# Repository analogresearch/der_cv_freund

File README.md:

# LITTLE████ CV Modul

Am CV Output liegt immer der Wert vom LB Input.
Am LB Output liegt wenn CV Input nicht eingesteckt ist der Wert vom LB Input.
         "     ... wenn CV Input eingesteckt ist der Wert vom CV Input.

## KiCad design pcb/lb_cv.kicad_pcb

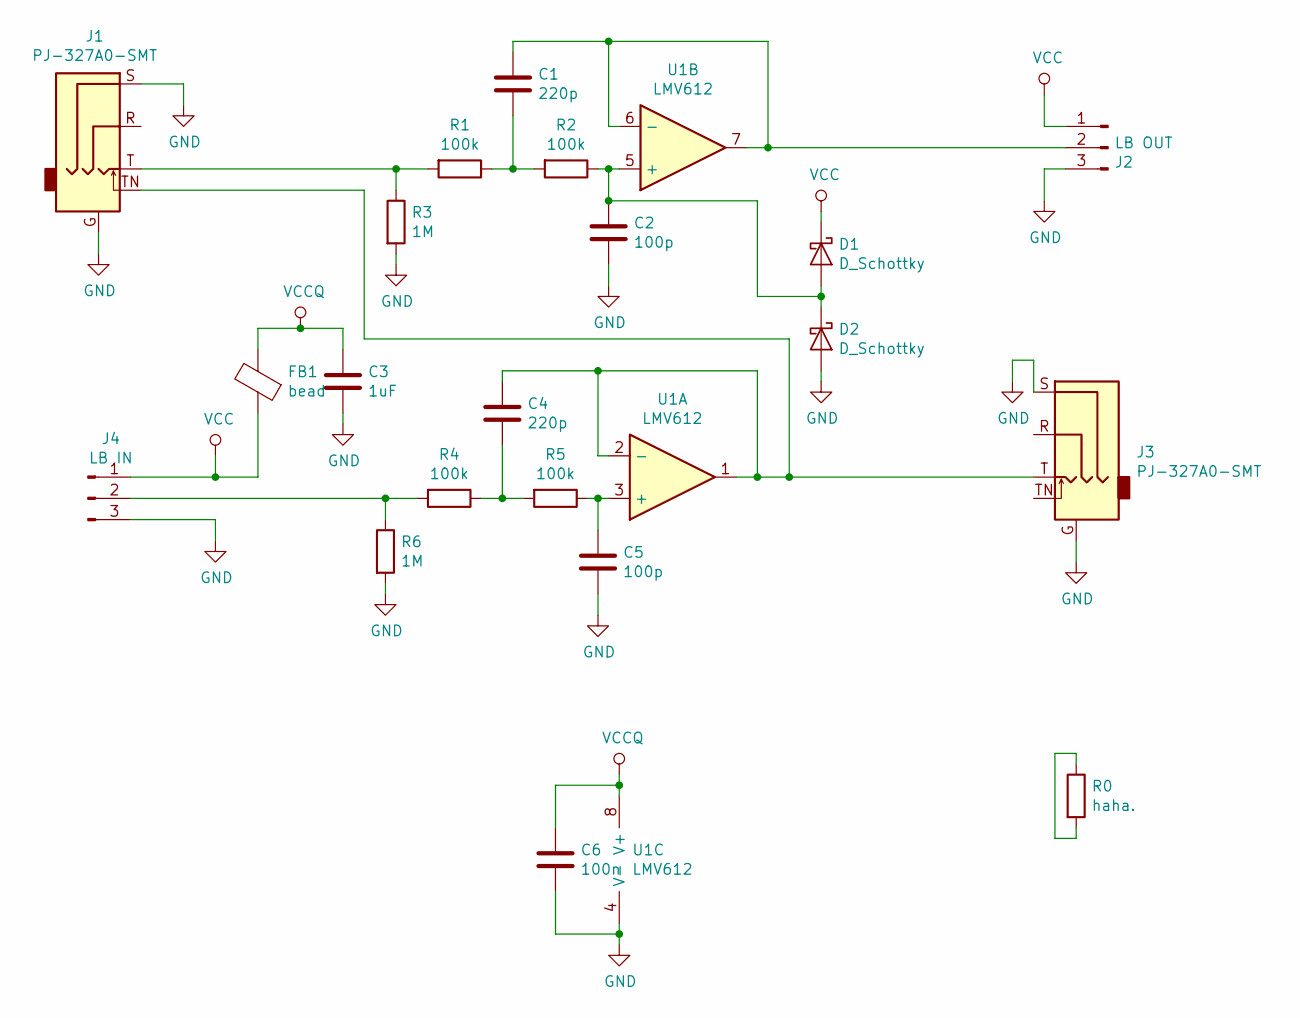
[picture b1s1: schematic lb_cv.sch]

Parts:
C1, C4: 220p; C_0805_2012Metric; LCSC CL21B221KBANNNC
C2, C5: 100p; C_0805_2012Metric; LCSC CL21C101JBANNNC
C3: 1uF; C_0805_2012Metric; LCSC CL21B105KBFNNNE
C6: 100n; C_0805_2012Metric; LCSC CC0805KRX7R9BB104
D1, D2: D_Schottky; D_SOD-123; LCSC B5819W
FB1: bead; L_0805_2012Metric; LCSC GZ2012D101TF
J1, J3: PJ-327A0-SMT
J2: LB OUT; bitsnaps_output
J4: LB IN; bitsnaps_input
R0: haha.; R_1206_3216Metric
R1, R2, R4, R5: 100k; R_0805_2012Metric; LCSC 0805W8F1003T5E
R3, R6: 1M; R_0805_2012Metric; LCSC 0805W8F1004T5E
U1: LMV612; VSSOP-8_3.0x3.0mm_P0.65mm; LCSC LMV612MMX/NOPB

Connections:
GND: C2.1, C3.2, C5.1, C6.2, D2.2 (A), J1.G, J1.S, J2.3, J3.G, J3.S, J4.3, R3.2, R6.2, U1.4 (V-)
unnamed: C1.1, J2.2, U1.6 (-), U1.7
unnamed: C1.2, R1.1, R2.2
unnamed: C2.2, D1.2 (A), D2.1 (K), R2.1, U1.5 (+)
unnamed: C4.1, J1.TN, J3.T, U1.1, U1.2 (-)
unnamed: C4.2, R4.1, R5.2
unnamed: C5.2, R5.1, U1.3 (+)
unnamed: J1.T, R1.2, R3.1
unnamed: J4.2, R4.2, R6.1
unnamed: R0.1, R0.2
VCC: D1.1 (K), FB1.1, J2.1, J4.1
VCCQ: C3.1, C6.1, FB1.2, U1.8 (V+)

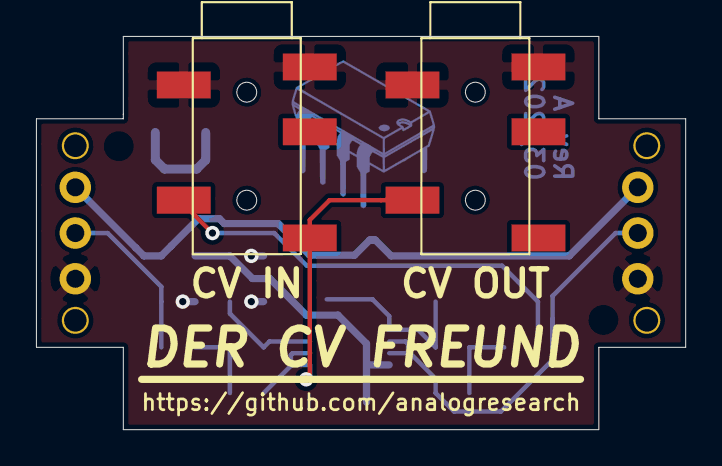
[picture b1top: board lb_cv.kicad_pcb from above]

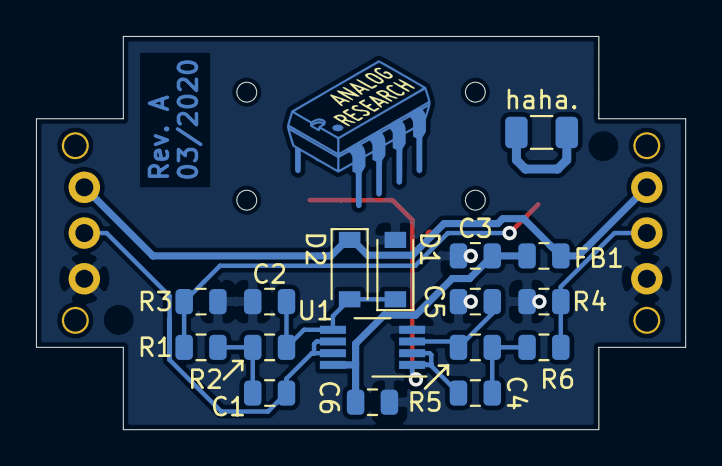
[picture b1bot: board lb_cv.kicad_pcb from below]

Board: 2 copper layers, 36.1 x 21.8 mm, 22 parts (18 on the bottom side), 12 nets.

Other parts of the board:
Ref**: Val**; logo-analogresearch-10mm

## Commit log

2020-05-06 initial
2020-12-02 added pcb layout
